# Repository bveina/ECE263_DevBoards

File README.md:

# ECE 263 Breakout Boards
There are three revisions of the ECE 263 breakout board. each is published in this repository.

each folder contains the Eagle files, a pdf of each schematic, a gerber folder,and two png renders of the board, top and bottom.

## [Version 1 - The White Board](./ECE263_breakout_V1)
## [Version 2 - The Green Board](./ECE263_breakout_V2)
## [Version 3 - The Red Board](./ECE263_breakout_V3)

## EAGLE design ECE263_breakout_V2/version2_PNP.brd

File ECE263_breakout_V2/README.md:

# ECE 263 Breakout Board Version 2
This repository is the public repo for the version one board for ECE263 "The Green Board"
It is targeted towards the Xplained Mini328pb not all features will be available if connected to an arduino.
this repo contains the original board files, and renders of the Schematic and Pcb (top and bottom) hosted here for easy reference.

## Potentiometers
Three potentiometers are connected across the power rail with wipers connected to the Analog to Digital Converter (ADC) pins.
- 328p pins PORT: C0, C1, C2

## Buttons
Three Momentary buttons are hooked up the processor to pull the inputs to ground when pressed.
Pull up resistors are onboard so the internal pull ups of the 328p/328pb don't need be activated.
- 328p pins: PORTE 0,1,2

## Seven Segment Display
A socket is provided for a 4 digit seven segment display with common Cathodes.

- Digit Enables:
 - 328p: PORTB 0,1,2,3
- Anodes (abcdefg.):
 - 328p: PORTD 0,1,2,3,4,5,6,7

## RGB led
A SMD Common Anode LED is included on the expansion board. (this version's anode is tied high, see version3 for a better option)
each Cathode is connected to a PWM capable Pin.
Color Cathodes (BGR):
- 328p: PORT B3,B1,D6
Anode:
- Tied High

## Speaker
A SMD peizo speaker is enabled by bringing PE3 high then can be controlled by toggling PD2.
D2 is also the modulator output on the atmega 328pb.

## Expansion Connector
3 external connections are provided on PE0,PB0,PE1.
these have external pullups making them useful for a thermistor or external buttons. they are also the processors Input Capture pins

# SPI Connector
A six pin connector is located under the seven segment display to allow the connection of a  [MAX7221 breakout](https://github.com/bveina/Max7221-Driver).
or any SPI device.
pinout:
1. MOSI0
2. MISO0
3. GND
4. VCC
5. SCK0
6. PB2 (SS0)

# I2C:registered: / TWI Expansion
a 4 pin two wire interface is broken out for connection to external devices
1. GND
2. VCC
3. SDA0/PC4
4. SCL0/PC5

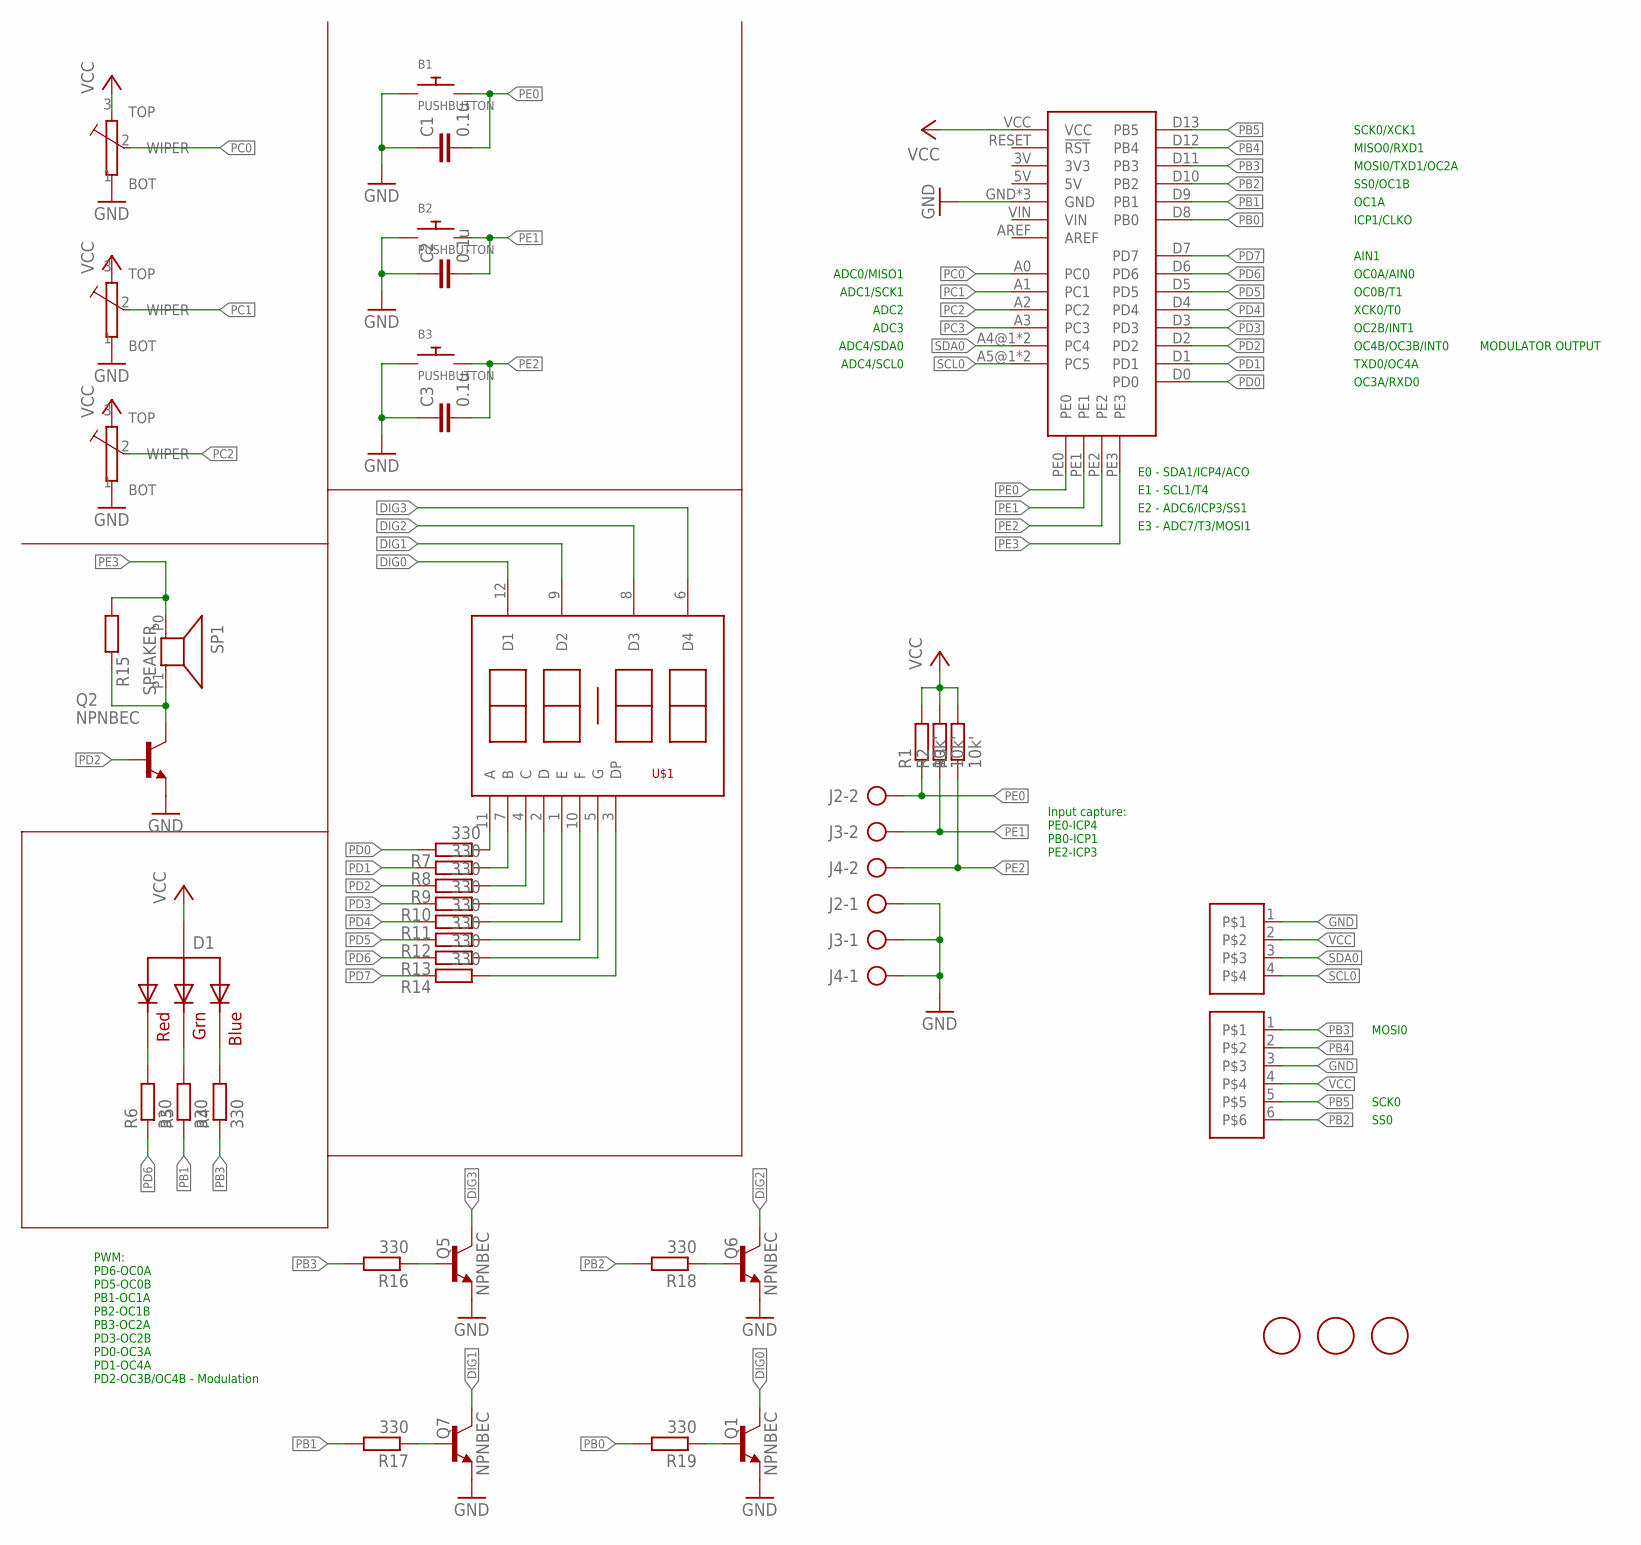
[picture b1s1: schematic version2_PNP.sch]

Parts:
B1, B2, B3: PUSHBUTTON; BUTTON_EVPBF
C1, C2, C3: 0.1u; C0805
D1: RGB_CA; PLCC-4
J1: M04F; 1X04_FEMALE
J2, J3, J4: 1X02CLEAN; 1X02_CLEAN
Q1, Q2, Q5, Q6, Q7: NPNBEC; SOT23
R1, R2, R3: 10k'; R0805
R4, R5, R6, R7, R8, R9, R10, R11, R12, R13, R14, R16, R17, R18, R19: 330; R0805
R15: R-EU_R0805; R0805
SP1: SPEAKER; PKMCS_SPEAKER
TR1, TR2, TR3: TRIMMTHUMB; RV09
U2: XPLAINEDMINI328PB; XPLAINEDMINI328P
U$1: 4DIG_7SEG_CATHODE; 4DIG_7SEG_CLOCK
U$2: M06F; 1X06_FEMALE
U$3, U$4, U$5: FIDUCIAL; FIDUCIAL_1MM

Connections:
A: R7.1, U$1.11 (A)
B: R8.1, U$1.7 (B)
C: R9.1, U$1.4 (C)
D: R10.1, U$1.2 (D)
DIG0: Q1.3 (C), U$1.12 (D1)
DIG1: Q7.3 (C), U$1.9 (D2)
DIG2: Q6.3 (C), U$1.8 (D3)
DIG3: Q5.3 (C), U$1.6 (D4)
DP: R14.1, U$1.3 (DP)
E: R11.1, U$1.1 (E)
F: R12.1, U$1.10 (F)
G: R13.1, U$1.5 (G)
GND: B1.A1, B1.A2, B2.A1, B2.A2, B3.A1, B3.A2, C1.1, C2.1, C3.1, J1.1, J2.1, J3.1, J4.1, Q1.2 (E), Q2.2 (E), Q5.2 (E), Q6.2 (E), Q7.2 (E), TR1.1 (BOT), TR2.1 (BOT), TR3.1 (BOT), U2.GND, U2.GND1 (GND), U2.GND2 (GND), U$2.3
unnamed: D1.P2 (BLUE), R4.2
unnamed: D1.P3 (GREEN), R5.2
unnamed: D1.P4 (RED), R6.2
unnamed: Q2.3 (C), R15.2, SP1.P1 (2)
unnamed: Q5.1 (B), R16.1
unnamed: Q1.1 (B), R19.1
unnamed: Q6.1 (B), R18.1
unnamed: Q7.1 (B), R17.1
PB0: R19.2, U2.D8 (PB0)
PB1: R5.1, R17.2, U2.D9 (PB1)
PB2: R18.2, U2.D10 (PB2), U$2.6
PB3: R4.1, R16.2, U2.D11 (PB3), U$2.1
PB4: U2.D12 (PB4), U$2.2
PB5: U2.D13 (PB5), U$2.5
PC0: TR1.2 (WIPER), U2.A0 (PC0)
PC1: TR2.2 (WIPER), U2.A1 (PC1)
PC2: TR3.2 (WIPER), U2.A2 (PC2)
PC3: U2.A3 (PC3)
PD0: R7.2, U2.D0
PD1: R8.2, U2.D1
PD2: Q2.1 (B), R9.2, U2.D2
PD3: R10.2, U2.D3
PD4: R11.2, U2.D4
PD5: R12.2, U2.D5
PD6: R6.1, R13.2, U2.D6
PD7: R14.2, U2.D7
PE0: B1.B1, B1.B2, C1.2, J2.2, R1.1, U2.PE0
PE1: B2.B1, B2.B2, C2.2, J3.2, R2.1, U2.PE1
PE2: B3.B1, B3.B2, C3.2, J4.2, R3.1, U2.PE2
PE3: R15.1, SP1.P0 (1), U2.PE3
SCL0: J1.4, U2.A5@1 (PC5), U2.A5@2 (PC5)
SDA0: J1.3, U2.A4@1 (PC4), U2.A4@2 (PC4)
VCC: D1.P1 (VCC), J1.2, R1.2, R2.2, R3.2, TR1.3 (TOP), TR2.3 (TOP), TR3.3 (TOP), U2.VCC, U$2.4

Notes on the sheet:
ICP1/CLKO
OC1A
SS0/OC1B
MOSI0/TXD1/OC2A
MISO0/RXD1
SCK0/XCK1
AIN1
OC0A/AIN0
OC0B/T1
XCK0/T0
OC2B/INT1
TXD0/OC4A
OC3A/RXD0
OC4B/OC3B/INT0
ADC0/MISO1
ADC1/SCK1
ADC2
ADC3
ADC4/SDA0
ADC4/SCL0
E0 - SDA1/ICP4/ACO
E1 - SCL1/T4
E2 - ADC6/ICP3/SS1
E3 - ADC7/T3/MOSI1
MODULATOR OUTPUT
Input capture: PE0-ICP4 PB0-ICP1 PE2-ICP3
PWM: PD6-OC0A PD5-OC0B PB1-OC1A PB2-OC1B PB3-OC2A PD3-OC2B PD0-OC3A PD1-OC4A PD2-OC3B/OC4B - Modulation
MOSI0
SCK0
SS0

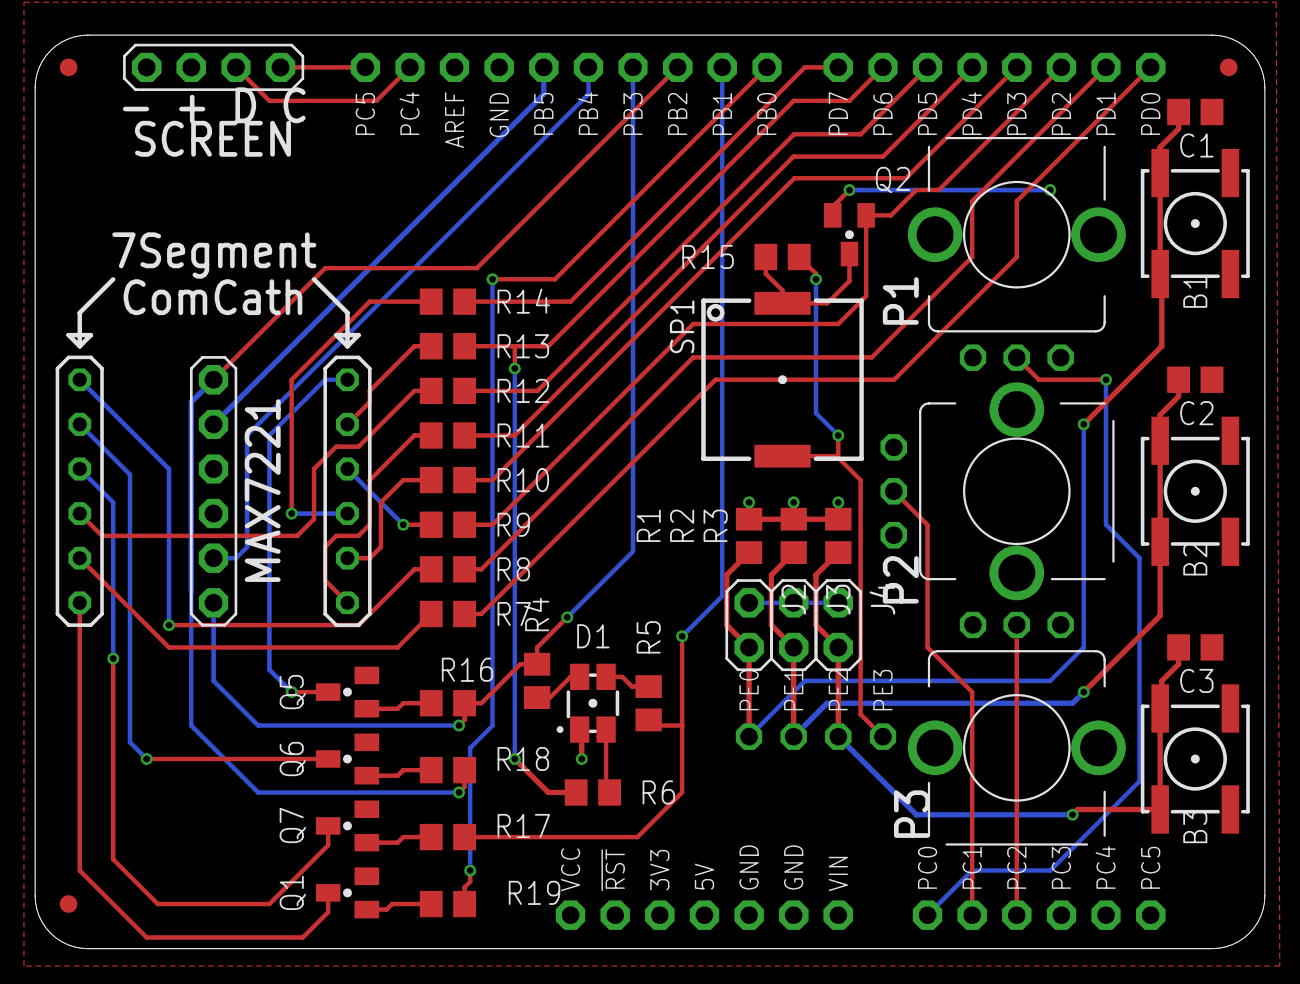
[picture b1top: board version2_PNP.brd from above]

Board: 2 copper layers, 70.0 x 52.0 mm, 45 parts (0 on the bottom side), 45 nets.

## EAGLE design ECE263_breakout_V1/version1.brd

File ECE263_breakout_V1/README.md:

# ECE 263 Breakout Board Version 1
This repository is the public repo for the version one board for ECE160/263 "the White Board"
it contains the original board files, and renders of the Schematic and Pcb (top and bottom) hosted here for easy reference.

This board was originally designed to mate with a standard arduino uno. but will also work with and atmel Xplained mini 328p or pb

## Potentiometers
Three potentiometers are connected across the power rail with wipers connected to the Analog to Digital Converter (ADC) pins.
- Arduino pins: A0, A1, A2
- 328p pins PORT: C0, C1, C2

## Buttons
Three Momentary buttons are hooked up the processor to pull the inputs to ground when pressed.
Pull up resistors are onboard so the internal pull ups of the 328p/328pb don't need be activated.
- Arduino pins: A3, A4, A5
- 328p pins: PORT C3, C4, C5

## Seven Segment Display
A socket is provided for a 4 digit seven segment display with common Cathodes.
Jumpers 3,4,5 must be set to enable either the seven segment display or the RGB led. Only one can be used at a time.

- Digit Enables:
 - Arduino: Digital 8,9,10,11
 - 328p: PORTB 0,1,2,3
- Anodes (abcdefg.):
 - Arduino: Digital 0,1,2,3,4,5,6,7
 - 328p: PORTD 0,1,2,3,4,5,6,7

## RGB led
A 10MM RGB Common Anode LED is included on the expansion board but must be selected by moving jumpers 3,4,5.

Color Cathodes (BGR):
- Arduino: Digital 9,10,11
- 328p: PORTB 1,2,3
Anode:
- Arduino: Digital 12
- 328p: PORTB 4

## Speaker
A speaker is connected to Digital 13/ PORTB5.

The less this annoying buzzer is used, the better.
its constant buzzing is what led to a complete redesign of this board...

## Expansion Connector
3 external connections are provided on portC/analog pins 3,4,5.
these have external pullups making them useful for a thermistor or external buttons.

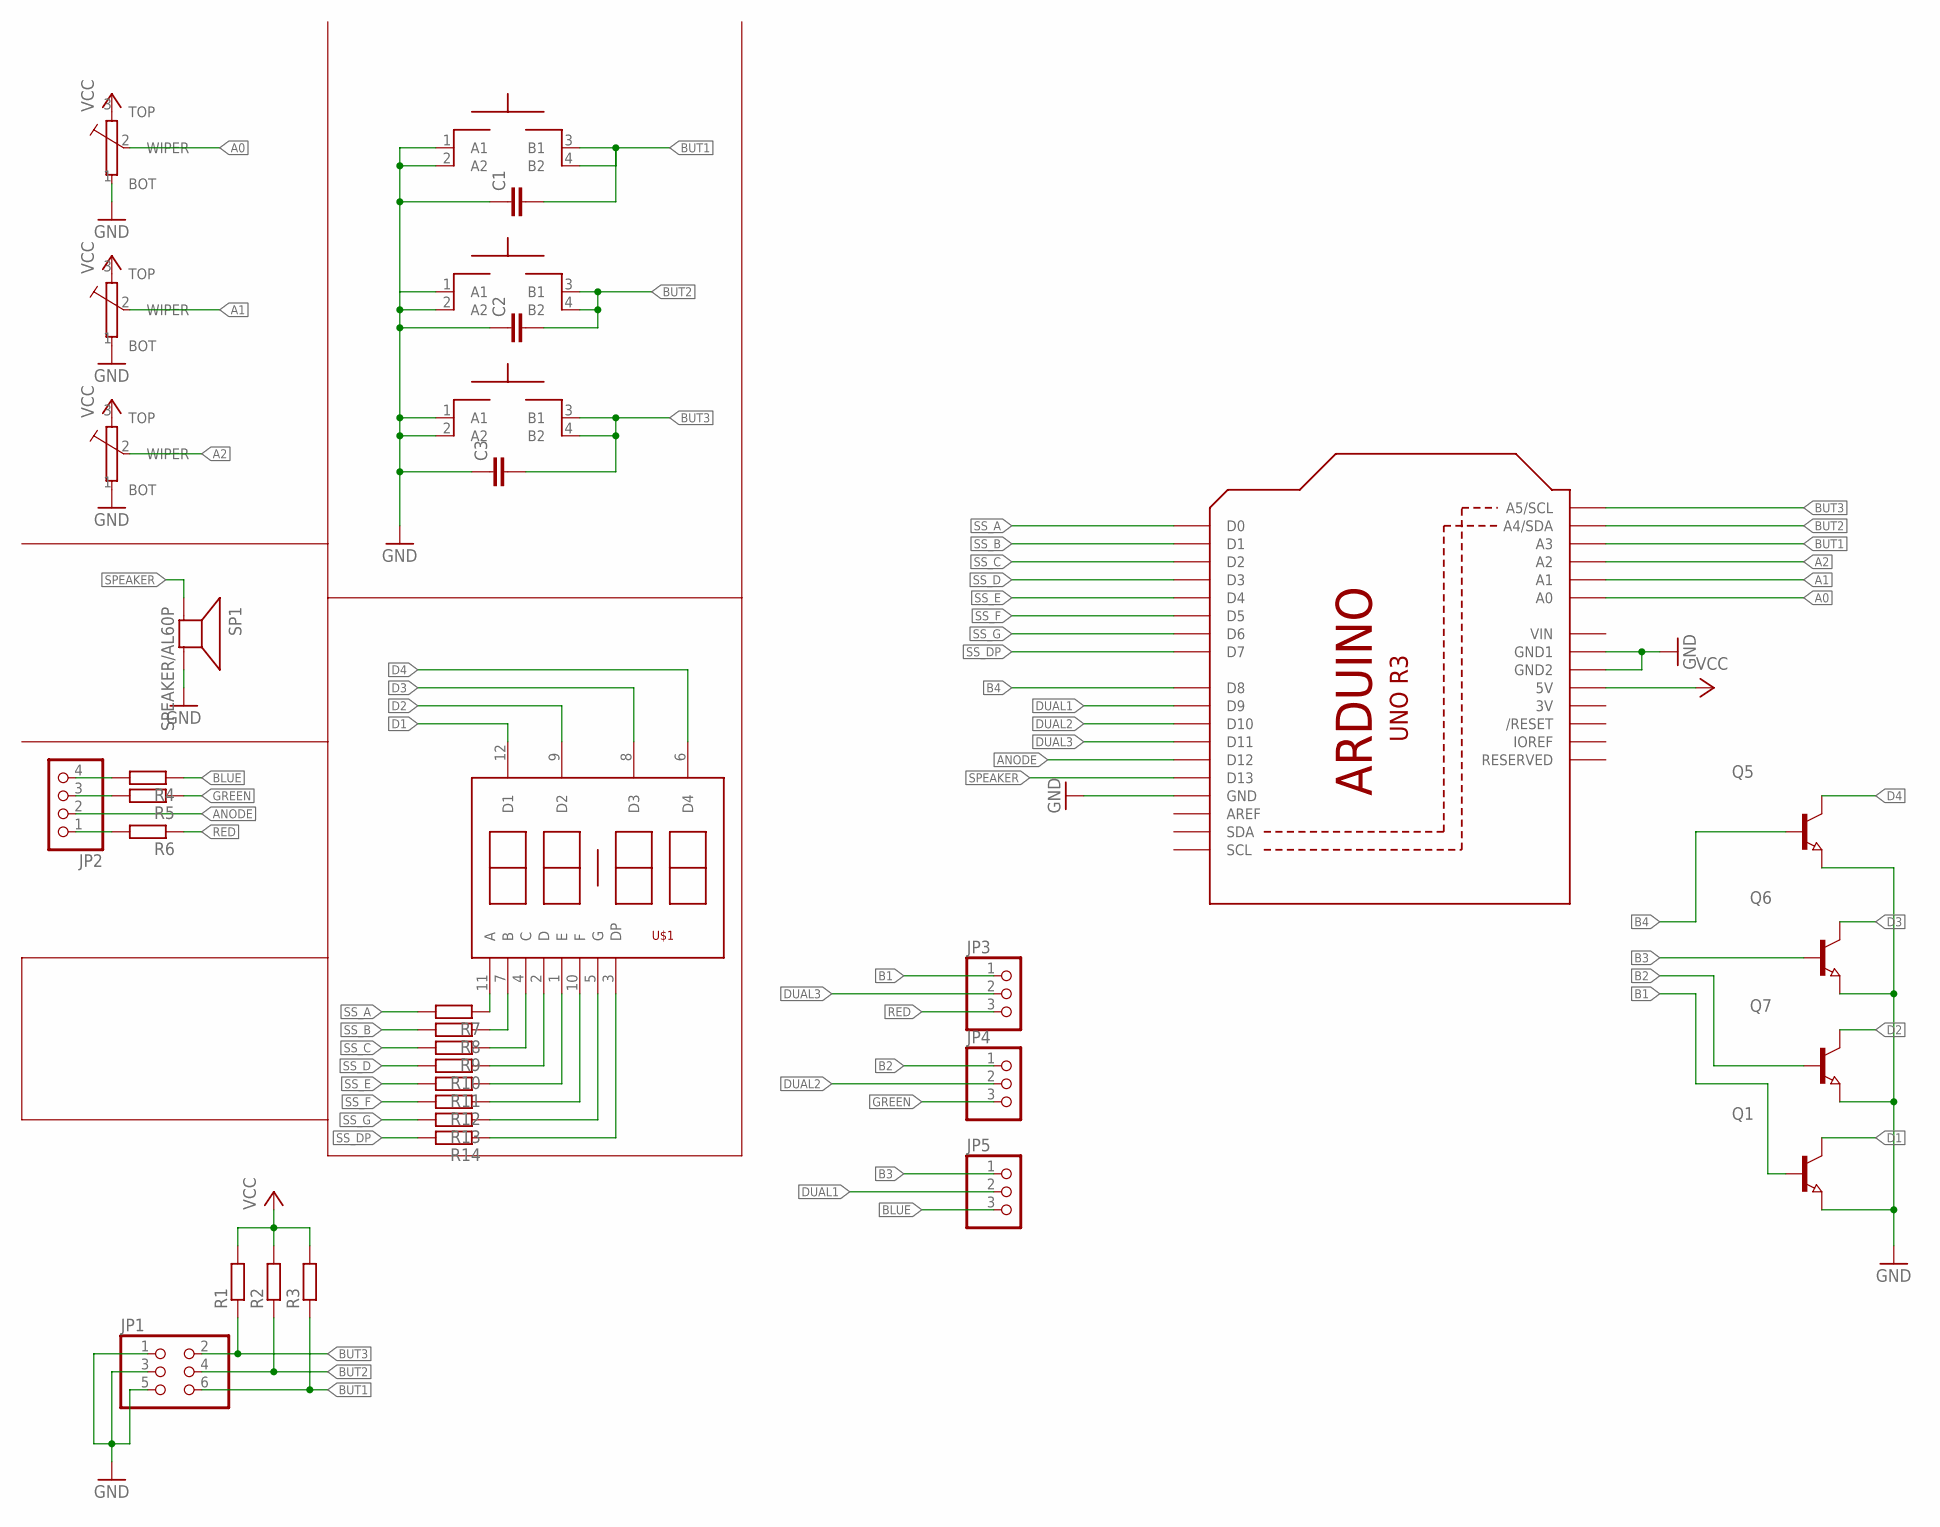
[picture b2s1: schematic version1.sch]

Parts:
C1, C2, C3: C-EUC0805; C0805
JP1: PINHD-2X3; 2X03
JP2: PINHD-1X4; 1X04
JP3, JP4, JP5: PINHD-1X3; 1X03
Q1, Q5, Q6, Q7: NPN-TRANSISTOR_SOT23; SOT23
R1, R2, R3, R4, R5, R6, R7, R8, R9, R10, R11, R12, R13, R14: R-EU_R0805; R0805
SP1: SPEAKER/AL60P; AL60P
SW1, SW2, SW3: MOMENTARYBUTTON; SPST_NO_SMD
TR1, TR2, TR3: TRIMMTHUMB; RV09
U1: ARDUINOR3-BPLACE
U$1: 4DIG_7SEG_CATHODE; 4DIG_7SEG_CLOCK

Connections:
3V: U1.3V
A0: TR1.2 (WIPER), U1.A0
A1: TR2.2 (WIPER), U1.A1
A2: TR3.2 (WIPER), U1.A2
ANODE: JP2.2, U1.D12
B1: JP3.1, Q1.1 (B)
B2: JP4.1, Q7.1 (B)
B3: JP5.1, Q6.1 (B)
B4: Q5.1 (B), U1.D8
BLUE: JP5.3, R4.1
BUT1: C1.2, JP1.6, R3.1, SW1.3 (B1), SW1.4 (B2), U1.A3
BUT2: C2.2, JP1.4, R2.1, SW2.3 (B1), SW2.4 (B2), U1.A4 (A4/SDA)
BUT3: C3.2, JP1.2, R1.1, SW3.3 (B1), SW3.4 (B2), U1.A5 (A5/SCL)
D1: Q1.3 (C), U$1.12 (D1)
D2: Q7.3 (C), U$1.9 (D2)
D3: Q6.3 (C), U$1.8 (D3)
D4: Q5.3 (C), U$1.6 (D4)
DUAL1: JP5.2, U1.D9
DUAL2: JP4.2, U1.D10
DUAL3: JP3.2, U1.D11
GND: C1.1, C2.1, C3.1, JP1.1, JP1.3, JP1.5, Q1.2 (E), Q5.2 (E), Q6.2 (E), Q7.2 (E), SP1.2 (-), SW1.1 (A1), SW1.2 (A2), SW2.1 (A1), SW2.2 (A2), SW3.1 (A1), SW3.2 (A2), TR1.1 (BOT), TR2.1 (BOT), TR3.1 (BOT), U1.GND, U1.GND1, U1.GND2
GREEN: JP4.3, R5.1
unnamed: JP2.4, R4.2
unnamed: JP2.3, R5.2
unnamed: JP2.1, R6.2
unnamed: R7.1, U$1.11 (A)
unnamed: R8.1, U$1.7 (B)
unnamed: R9.1, U$1.4 (C)
unnamed: R10.1, U$1.2 (D)
unnamed: R11.1, U$1.1 (E)
unnamed: R12.1, U$1.10 (F)
unnamed: R13.1, U$1.5 (G)
unnamed: R14.1, U$1.3 (DP)
RED: JP3.3, R6.1
SPEAKER: SP1.1 (+), U1.D13
SS_A: R7.2, U1.D0
SS_B: R8.2, U1.D1
SS_C: R9.2, U1.D2
SS_D: R10.2, U1.D3
SS_DP: R14.2, U1.D7
SS_E: R11.2, U1.D4
SS_F: R12.2, U1.D5
SS_G: R13.2, U1.D6
VCC: R1.2, R2.2, R3.2, TR1.3 (TOP), TR2.3 (TOP), TR3.3 (TOP), U1.5V
VIN: U1.VIN

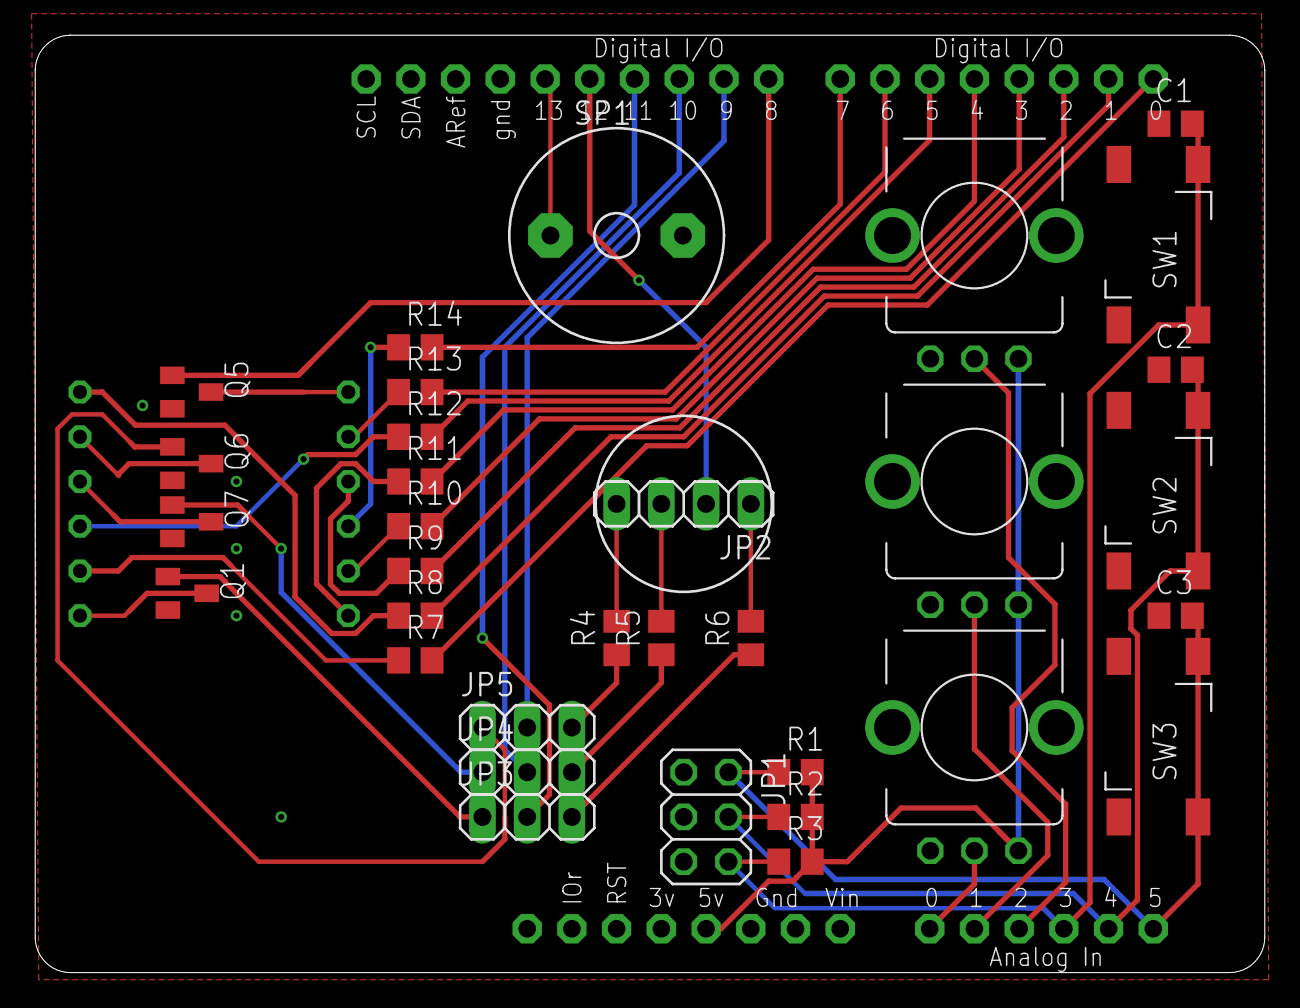
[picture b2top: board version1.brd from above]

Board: 2 copper layers, 69.8 x 53.2 mm, 35 parts (0 on the bottom side), 43 nets.

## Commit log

2021-05-15 initial file drop for public release
